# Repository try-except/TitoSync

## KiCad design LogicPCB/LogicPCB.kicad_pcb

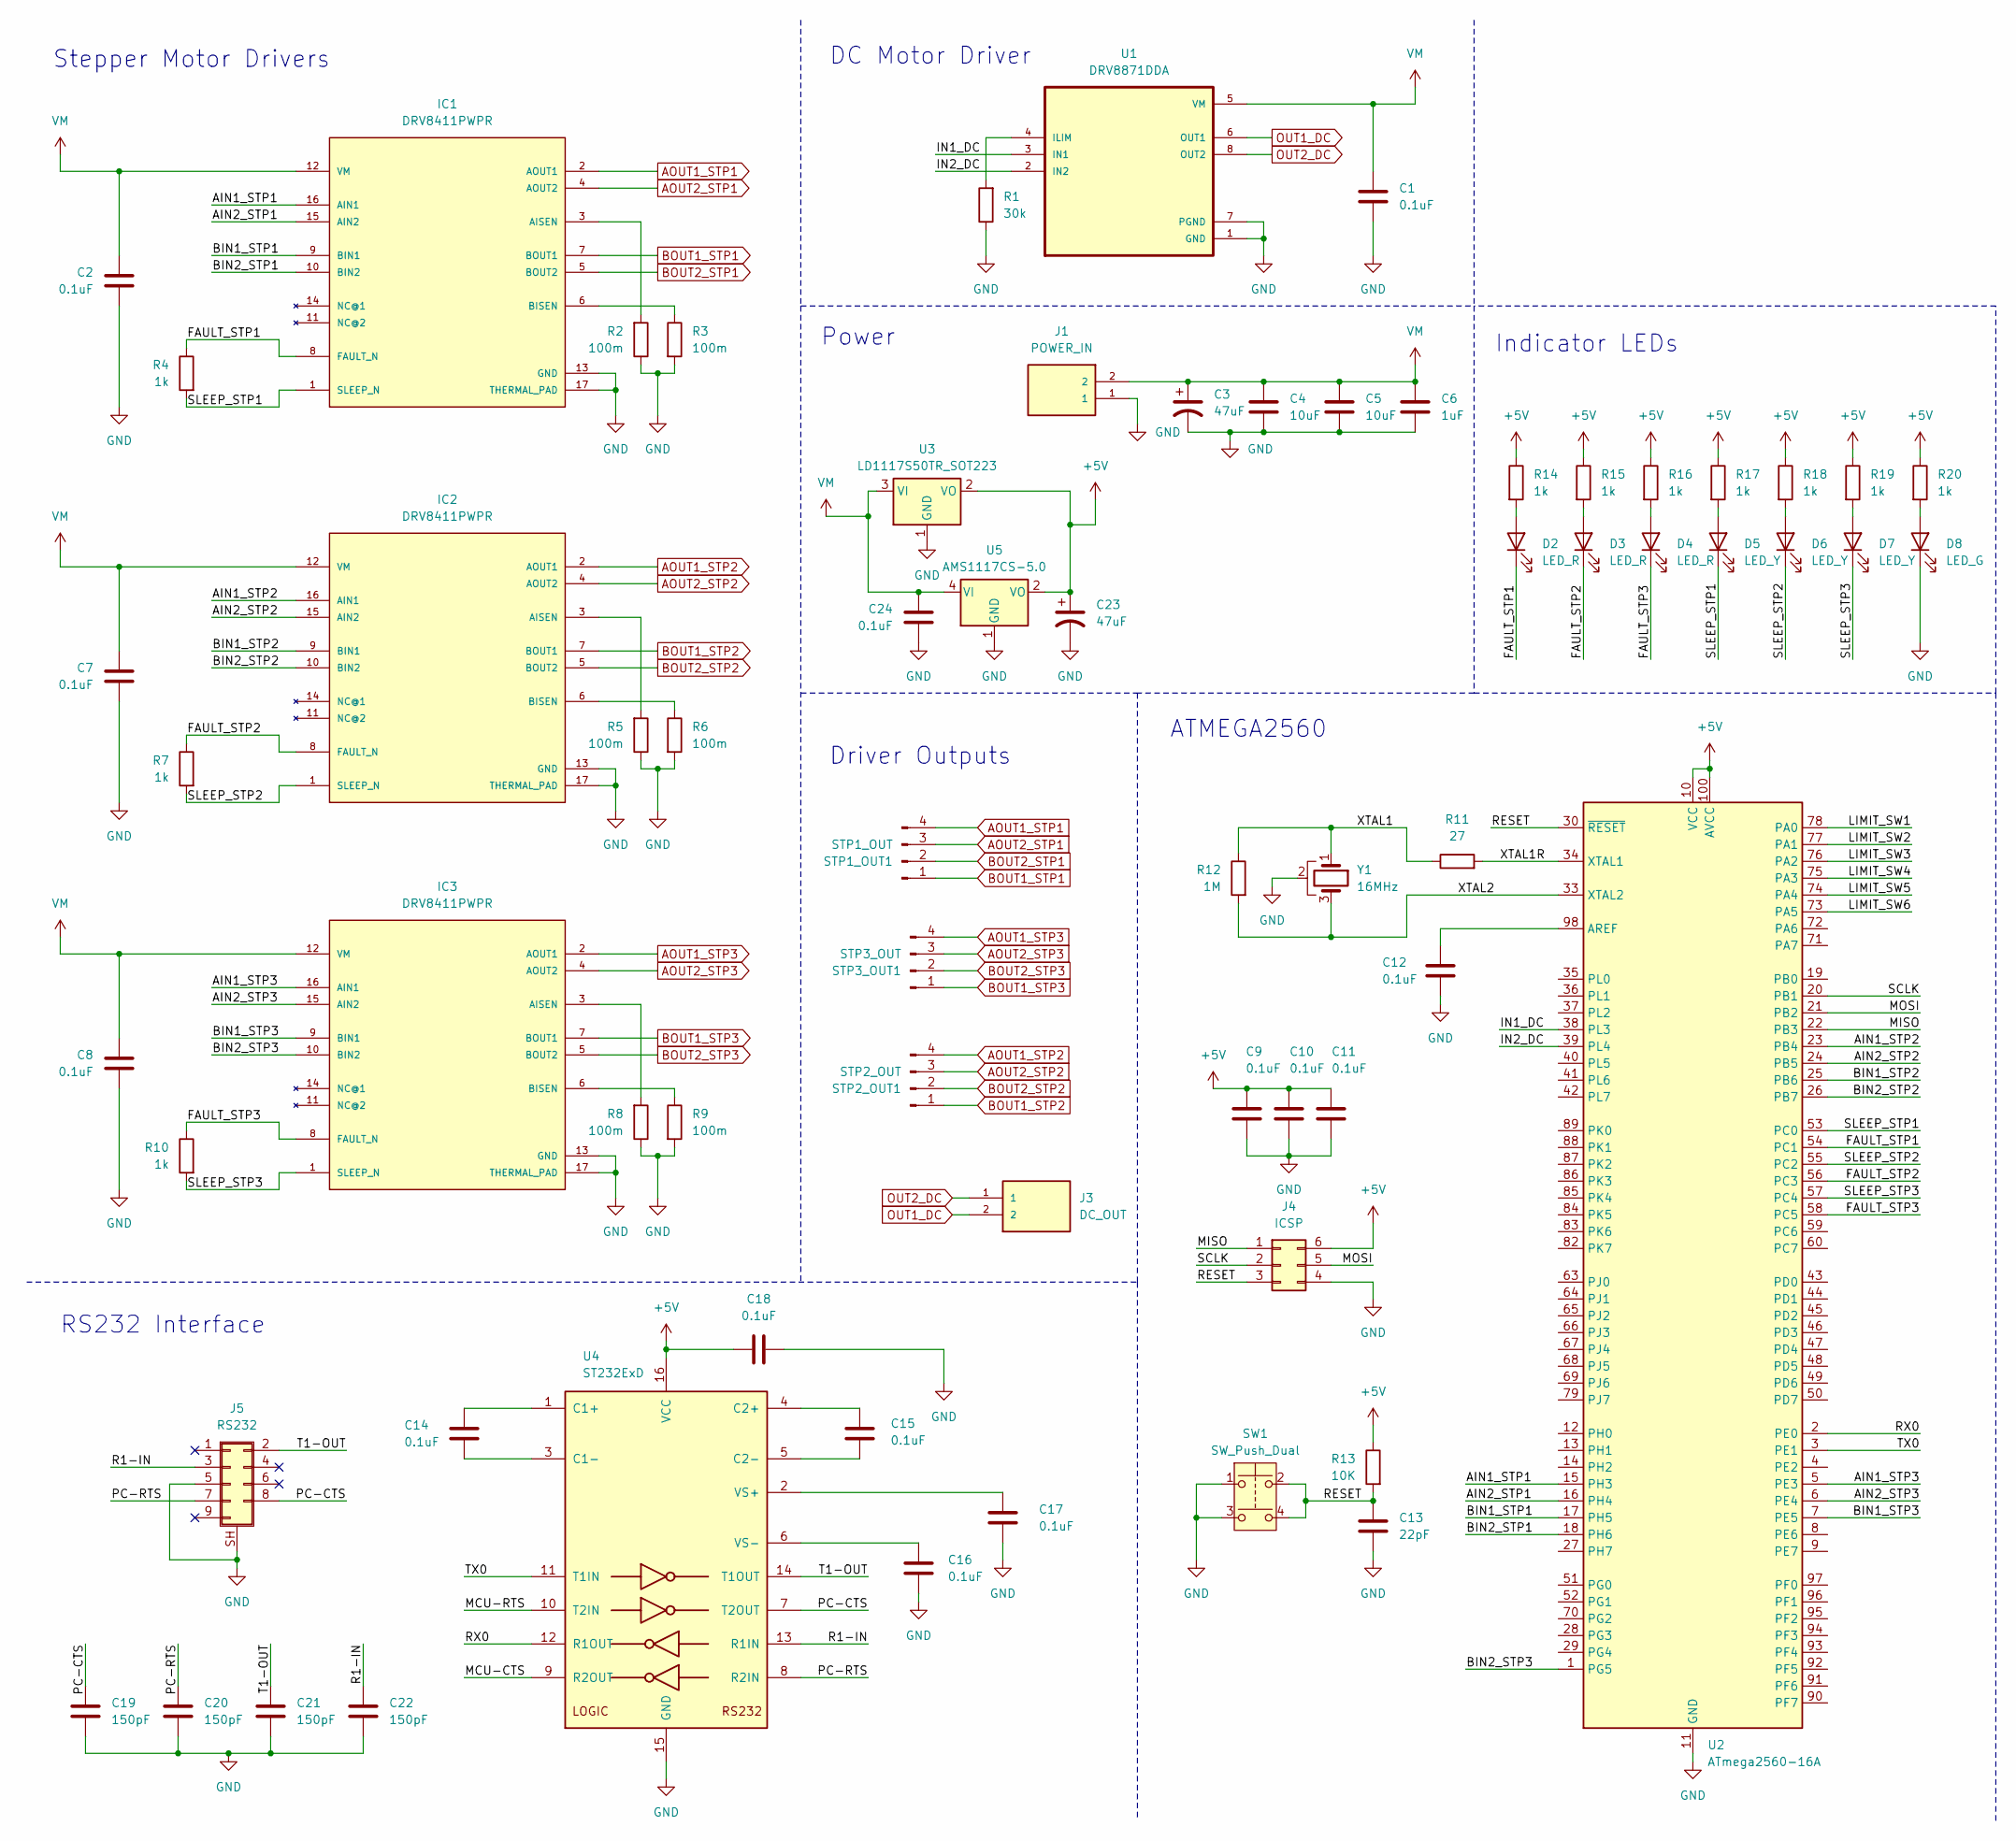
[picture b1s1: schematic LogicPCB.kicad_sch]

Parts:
C1, C2, C7, C8, C9, C10, C11, C12, C14, C15, C16, C17, C18, C24: 0.1uF; C_0402_1005Metric; PartNumber GRM155R71H104KE14D
C3, C23: 47uF; CP_Elec_6.3x5.4; PartNumber FVH035ADA470M0654
C4, C5: 10uF; C_1206_3216Metric; PartNumber C3216X7R1C106KT000N
C6: 1uF; C_0603_1608Metric; PartNumber GRT188R61H105ME13D
C13: 22pF; C_0402_1005Metric; PartNumber GRM155R71H104KE14D
C19, C20, C21, C22: 150pF; C_0402_1005Metric; PartNumber GRM1555C1H151JA01D
D2, D3, D4: LED_R; LED_0603_1608Metric
D5, D6, D7: LED_Y; LED_0603_1608Metric
D8: LED_G; LED_0603_1608Metric
IC1, IC2, IC3: DRV8411PWPR; HTSSOP-16-1EP_4.4x5mm_P0.65mm_EP3.4x5mm_Mask2.66x2.46mm; PartNumber DRV8411PWPR
J1: POWER_IN; TerminalBlock_MetzConnect_Type094_RT03502HBLU_1x02_P5.00mm_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; PARTREV 1.0
J3: DC_OUT; TerminalBlock_MetzConnect_Type094_RT03502HBLU_1x02_P5.00mm_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; PARTREV 1.0
J4: ICSP; PinHeader_2x03_P2.54mm_Vertical
J5: RS232; DSUB-9_Pins_Horizontal_P2.77x2.84mm_EdgePinOffset4.94mm_Hou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
R1: 30k; R_0805_2012Metric_Pad1.20x1.40mm_HandSolder; PartNumber 0805W8F3002T5E
R2, R3, R5, R6, R8, R9: 100m; R_1206_3216Metric; PartNumber 1206W4F100LT5E
R4, R7, R10, R14, R15, R16, R17, R18, R19, R20: 1k; R_0805_2012Metric; PartNumber 0805W8F1001T5E
R11: 27; R_0805_2012Metric
R12: 1M; R_0805_2012Metric
R13: 10K; R_0805_2012Metric
STP1_OUT1: STP1_OUT; JST_XH_B4B-XH-A_1x04_P2.50mm_Vertical
STP2_OUT1: STP2_OUT; JST_XH_B4B-XH-A_1x04_P2.50mm_Vertical
STP3_OUT1: STP3_OUT; JST_XH_B4B-XH-A_1x04_P2.50mm_Vertical
SW1: SW_Push_Dual; SW_Push_1P1T_NO_E-Switch_TL3301NxxxxxG
U1: DRV8871DDA; VREG_LM5017MR_NOPB; PartNumber DRV8871DDA
U2: ATmega2560-16A; TQFP-100_14x14mm_P0.5mm
U3: LD1117S50TR_SOT223; SOT-223-3_TabPin2
U4: ST232ExD; SOIC-16_3.9x9.9mm_P1.27mm
U5: AMS1117CS-5.0; SOIC-8_3.9x4.9mm_P1.27mm
Y1: 16MHz; Resonator_SMD_Murata_CSTxExxV-3Pin_3.0x1.1mm; PartNumber CSTNE16M0V530000R0

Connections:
+5V: C9.2, C10.2, C11.2, C18.1, C23.1, J4.6, R13.1, R14.1, R15.1, R16.1, R17.1, R18.1, R19.1, R20.1, U2.10 (VCC), U2.31 (VCC), U2.61 (VCC), U2.80 (VCC), U2.100 (AVCC), U3.2 (VO), U4.16 (VCC), U5.2 (VO), U5.3 (VO), U5.6 (VO), U5.7 (VO)
/AIN1_STP1: IC1.16 (AIN1), U2.15 (PH3)
/AIN1_STP2: IC2.16 (AIN1), U2.23 (PB4)
/AIN1_STP3: IC3.16 (AIN1), U2.5 (PE3)
/AIN2_STP1: IC1.15 (AIN2), U2.16 (PH4)
/AIN2_STP2: IC2.15 (AIN2), U2.24 (PB5)
/AIN2_STP3: IC3.15 (AIN2), U2.6 (PE4)
/BIN1_STP1: IC1.9 (BIN1), U2.17 (PH5)
/BIN1_STP2: IC2.9 (BIN1), U2.25 (PB6)
/BIN1_STP3: IC3.9 (BIN1), U2.7 (PE5)
/BIN2_STP1: IC1.10 (BIN2), U2.18 (PH6)
/BIN2_STP2: IC2.10 (BIN2), U2.26 (PB7)
/BIN2_STP3: IC3.10 (BIN2), U2.1 (PG5)
/FAULT_STP1: D2.1 (K), IC1.8 (FAULT_N), R4.1, U2.54 (PC1)
/FAULT_STP2: D3.1 (K), IC2.8 (FAULT_N), R7.1, U2.56 (PC3)
/FAULT_STP3: D4.1 (K), IC3.8 (FAULT_N), R10.1, U2.58 (PC5)
/IN1_DC: U1.3 (IN1), U2.38 (PL3)
/IN2_DC: U1.2 (IN2), U2.39 (PL4)
/LIMIT_SW1: U2.78 (PA0)
/LIMIT_SW2: U2.77 (PA1)
/LIMIT_SW3: U2.76 (PA2)
/LIMIT_SW4: U2.75 (PA3)
/LIMIT_SW5: U2.74 (PA4)
/LIMIT_SW6: U2.73 (PA5)
/MCU-CTS: U4.9 (R2OUT)
/MCU-RTS: U4.10 (T2IN)
/MISO: J4.1, U2.22 (PB3)
/MOSI: J4.5, U2.21 (PB2)
/PC-CTS: C19.1, J5.8, U4.7 (T2OUT)
/PC-RTS: C20.1, J5.7, U4.8 (R2IN)
/R1-IN: C22.1, J5.3, U4.13 (R1IN)
/RESET: C13.2, J4.3, R13.2, SW1.2, SW1.4, U2.30 (~RESET); also elsewhere on the board
/RX0: U2.2 (PE0), U4.12 (R1OUT)
/SCLK: J4.2, U2.20 (PB1)
/SLEEP_STP1: D5.1 (K), IC1.1 (SLEEP_N), R4.2, U2.53 (PC0)
/SLEEP_STP2: D6.1 (K), IC2.1 (SLEEP_N), R7.2, U2.55 (PC2)
/SLEEP_STP3: D7.1 (K), IC3.1 (SLEEP_N), R10.2, U2.57 (PC4)
/T1-OUT: C21.1, J5.2, U4.14 (T1OUT)
/TX0: U2.3 (PE1), U4.11 (T1IN)
/XTAL1: R11.1, R12.1, Y1.1
/XTAL1R: R11.2, U2.34 (XTAL1)
/XTAL2: R12.2, U2.33 (XTAL2), Y1.3
AOUT1_STP1: IC1.2 (AOUT1), STP1_OUT1.4; also elsewhere on the board
AOUT1_STP2: IC2.2 (AOUT1), STP2_OUT1.4; also elsewhere on the board
AOUT1_STP3: IC3.2 (AOUT1), STP3_OUT1.4; also elsewhere on the board
AOUT2_STP1: IC1.4 (AOUT2), STP1_OUT1.3; also elsewhere on the board
AOUT2_STP2: IC2.4 (AOUT2), STP2_OUT1.3; also elsewhere on the board
AOUT2_STP3: IC3.4 (AOUT2), STP3_OUT1.3; also elsewhere on the board
BOUT1_STP1: IC1.7 (BOUT1), STP1_OUT1.1; also elsewhere on the board
BOUT1_STP2: IC2.7 (BOUT1), STP2_OUT1.1; also elsewhere on the board
BOUT1_STP3: IC3.7 (BOUT1), STP3_OUT1.1; also elsewhere on the board
BOUT2_STP1: IC1.5 (BOUT2), STP1_OUT1.2; also elsewhere on the board
BOUT2_STP2: IC2.5 (BOUT2), STP2_OUT1.2; also elsewhere on the board
BOUT2_STP3: IC3.5 (BOUT2), STP3_OUT1.2; also elsewhere on the board
GND: C1.1, C2.1, C3.2, C4.1, C5.1, C6.2, C7.1, C8.1, C9.1, C10.1, C11.1, C12.1, C13.1, C16.1, C17.1, C18.2, C19.2, C20.2, C21.2, C22.2, C23.2, C24.1, D8.1 (K), IC1.13 (GND), IC1.17 (THERMAL_PAD), IC2.13 (GND), IC2.17 (THERMAL_PAD), IC3.13 (GND), IC3.17 (THERMAL_PAD), J1.1, J4.4, J5.5, J5.SH (Shield), R1.1, R2.1, R3.2, R5.1, R6.2, R8.1, R9.2, SW1.1, SW1.3, U1.1 (GND), U1.7 (PGND), U2.11 (GND), U2.32 (GND), U2.62 (GND), U2.81 (GND), U2.99 (GND), U3.1 (GND), U4.15 (GND), U5.1 (GND), Y1.2; also elsewhere on the board
unnamed: D2.2 (A), R14.2
unnamed: D3.2 (A), R15.2
unnamed: D4.2 (A), R16.2
unnamed: D5.2 (A), R17.2
unnamed: D6.2 (A), R18.2
unnamed: D7.2 (A), R19.2
unnamed: D8.2 (A), R20.2
unnamed: IC1.3 (AISEN), R2.2
unnamed: IC1.6 (BISEN), R3.1
unnamed: IC2.3 (AISEN), R5.2
unnamed: IC2.6 (BISEN), R6.1
unnamed: IC3.3 (AISEN), R8.2
unnamed: IC3.6 (BISEN), R9.1
unnamed: R1.2, U1.4 (ILIM)
unnamed: C12.2, U2.98 (AREF)
unnamed: C14.2, U4.1 (C1+)
unnamed: C14.1, U4.3 (C1-)
unnamed: C15.2, U4.4 (C2+)
unnamed: C15.1, U4.5 (C2-)
unnamed: C17.2, U4.2 (VS+)
unnamed: C16.2, U4.6 (VS-)
OUT1_DC: J3.2, U1.6 (OUT1)
OUT2_DC: J3.1, U1.8 (OUT2)
VM: C1.2, C2.2, C3.1, C4.2, C5.2, C6.1, C7.2, C8.2, C24.2, IC1.12 (VM), IC2.12 (VM), IC3.12 (VM), J1.2, U1.5 (VM), U3.3 (VI), U5.4 (VI)

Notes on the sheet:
DC Motor Driver
Stepper Motor Drivers
Indicator LEDs
ATMEGA2560
RS232 Interface
Driver Outputs
Power

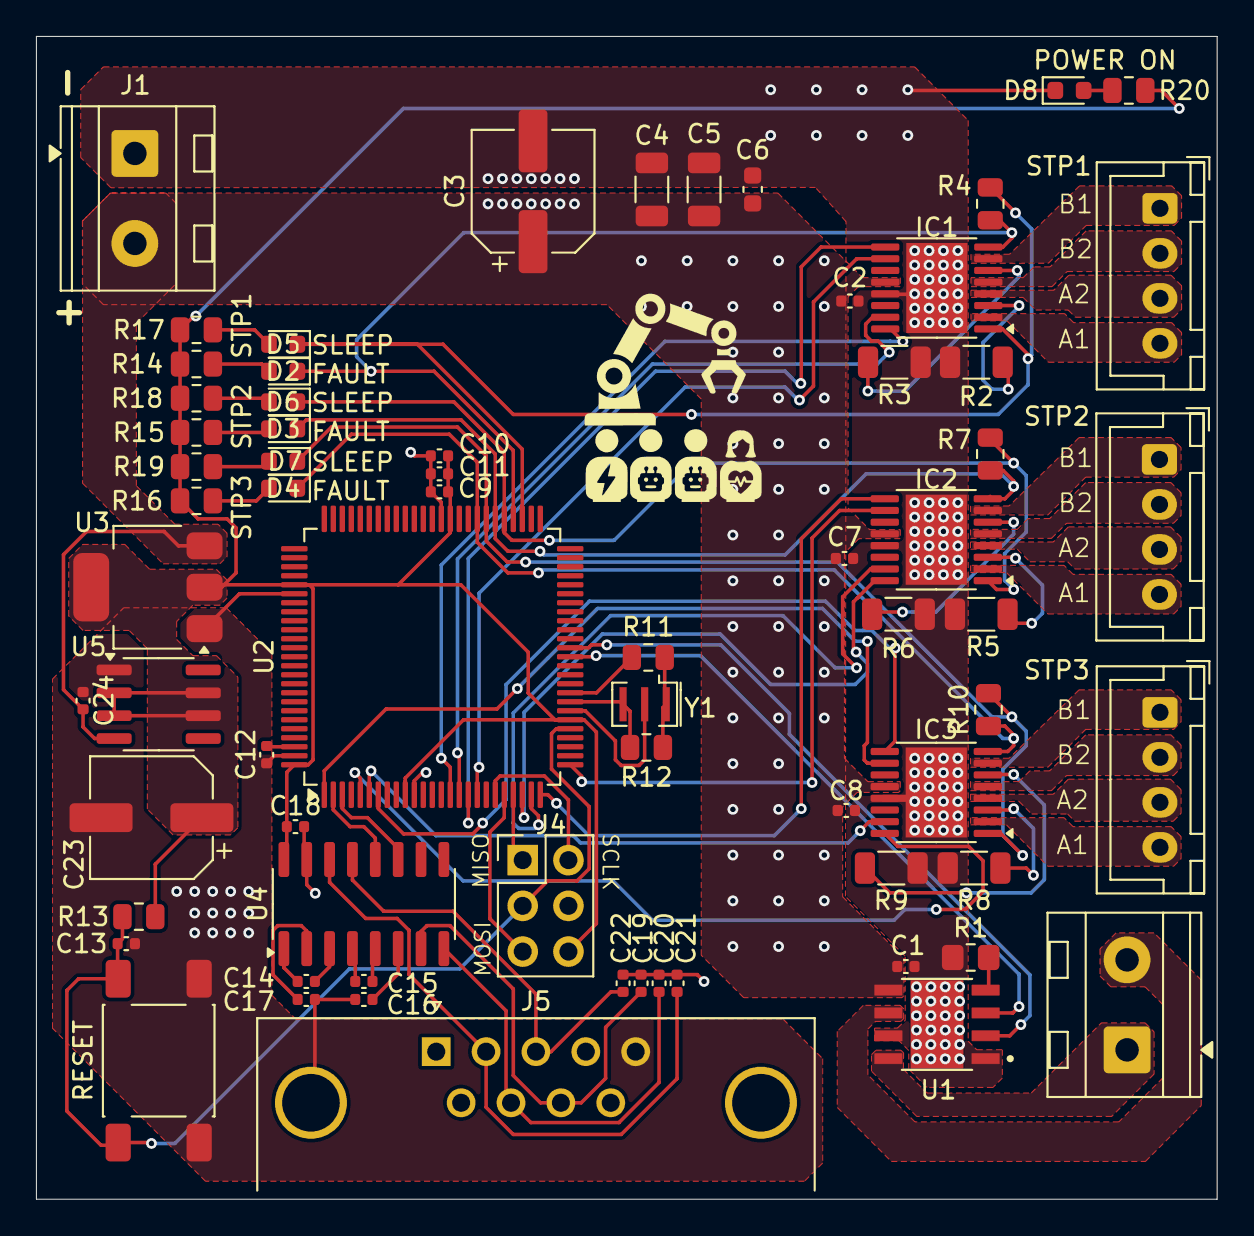
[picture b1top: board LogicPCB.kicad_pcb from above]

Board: 2 copper layers, 65.6 x 64.6 mm, 68 parts (0 on the bottom side), 71 nets.

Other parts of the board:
RESET: SW_Push_Dual; SW_Push_1P1T_NO_E-Switch_TL3301NxxxxxG
STP1: STP1_OUT; JST_XH_B4B-XH-A_1x04_P2.50mm_Vertical
STP2: STP2_OUT; JST_XH_B4B-XH-A_1x04_P2.50mm_Vertical
STP3: STP3_OUT; JST_XH_B4B-XH-A_1x04_P2.50mm_Vertical

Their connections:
/RESET: RESET.2; also elsewhere on the board
AOUT1_STP1: STP1.4; also elsewhere on the board
AOUT1_STP2: STP2.4; also elsewhere on the board
AOUT1_STP3: STP3.4; also elsewhere on the board
AOUT2_STP1: STP1.3; also elsewhere on the board
AOUT2_STP2: STP2.3; also elsewhere on the board
AOUT2_STP3: STP3.3; also elsewhere on the board
BOUT1_STP1: STP1.1; also elsewhere on the board
BOUT1_STP2: STP2.1; also elsewhere on the board
BOUT1_STP3: STP3.1; also elsewhere on the board
BOUT2_STP1: STP1.2; also elsewhere on the board
BOUT2_STP2: STP2.2; also elsewhere on the board
BOUT2_STP3: STP3.2; also elsewhere on the board
GND: RESET.1; also elsewhere on the board

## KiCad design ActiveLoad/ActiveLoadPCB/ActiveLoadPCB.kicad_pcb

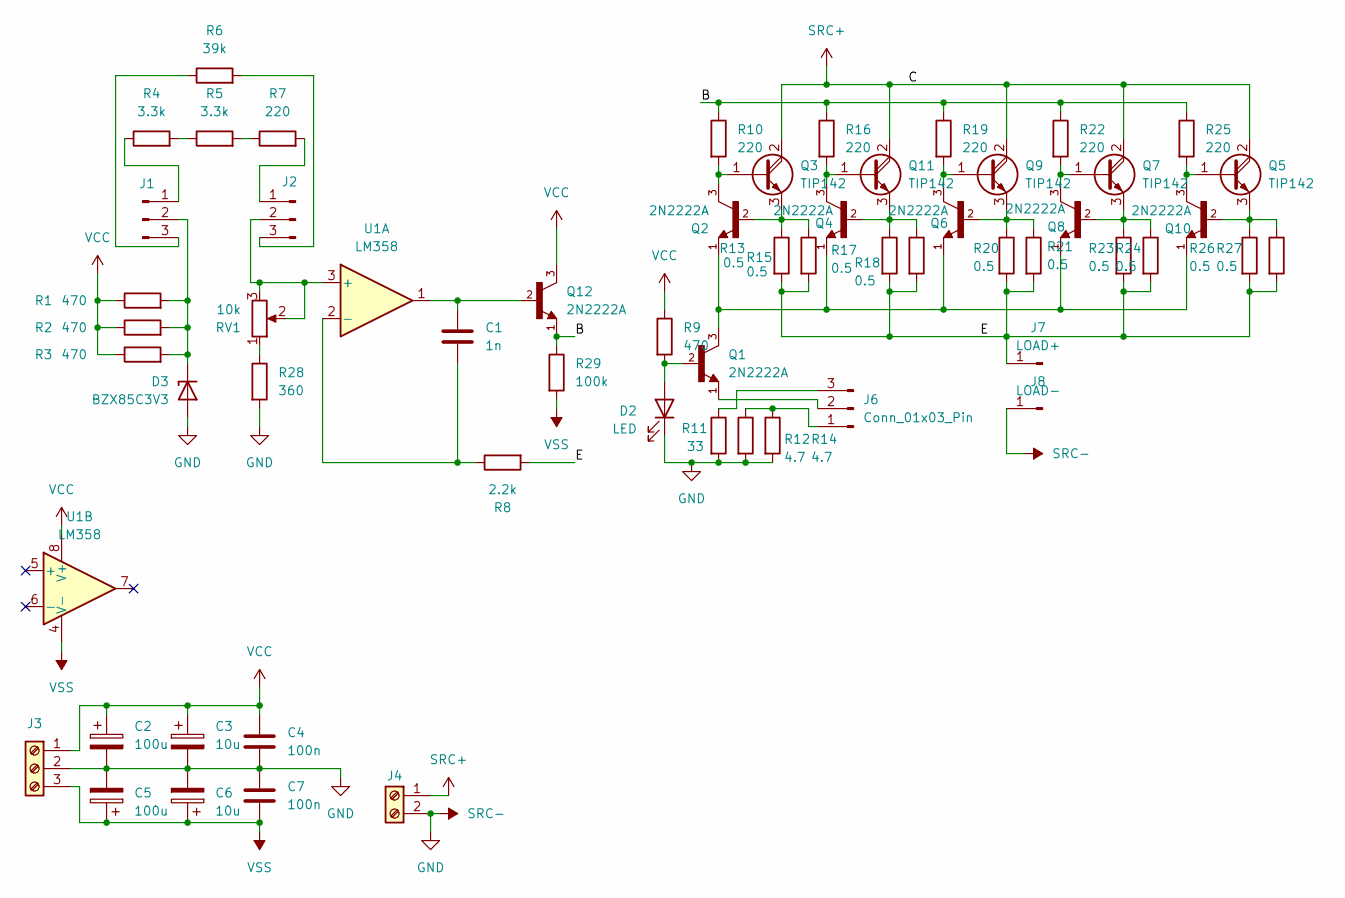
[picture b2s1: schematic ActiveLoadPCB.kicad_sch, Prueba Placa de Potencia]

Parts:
C1: 1n; C_Disc_D5.0mm_W2.5mm_P2.50mm
C2, C5: 100u; CP_Radial_D5.0mm_P2.50mm
C3, C6: 10u; CP_Radial_D5.0mm_P2.50mm
C4, C7: 100n; C_Disc_D5.0mm_W2.5mm_P2.50mm
D2: LED; LED_D3.0mm
D3: BZX85C3V3; D_T-1_P5.08mm_Horizontal
J1, J2, J6: Conn_01x03_Pin; PinHeader_1x03_P2.54mm_Vertical
J3: Screw_Terminal_01x03; TerminalBlock_MetzConnect_Type055_RT01503HDWU_1x03_P5.00mm_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
J4: Screw_Terminal_01x02; TerminalBlock_MetzConnect_Type055_RT01502HDWU_1x02_P5.00mm_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
J7: LOAD+; MountingHole_4.3mm_M4_DIN965_Pad
J8: LOAD-; MountingHole_4.3mm_M4_DIN965_Pad
Q1, Q2, Q4, Q6, Q8, Q10, Q12: 2N2222A; TO-92L_Inline_Wide; PARTREV N/A
Q3, Q5, Q7, Q9, Q11: TIP142; TO-247-3_Vertical
R1, R2, R3, R9: 470; R_Axial_DIN0207_L6.3mm_D2.5mm_P7.62mm_Horizontal
R4, R5: 3.3k; R_Axial_DIN0207_L6.3mm_D2.5mm_P7.62mm_Horizontal
R6: 39k; R_Axial_DIN0207_L6.3mm_D2.5mm_P7.62mm_Horizontal
R7, R10, R16, R19, R22, R25: 220; R_Axial_DIN0207_L6.3mm_D2.5mm_P7.62mm_Horizontal
R8: 2.2k; R_Axial_DIN0207_L6.3mm_D2.5mm_P7.62mm_Horizontal
R11: 33; R_Axial_DIN0207_L6.3mm_D2.5mm_P7.62mm_Horizontal
R12, R14: 4.7; R_Axial_DIN0207_L6.3mm_D2.5mm_P7.62mm_Horizontal
R13, R15, R17, R18, R20, R21, R23, R24, R26, R27: 0.5; R_Axial_DIN0309_L9.0mm_D3.2mm_P12.70mm_Horizontal
R28: 360; R_Axial_DIN0207_L6.3mm_D2.5mm_P7.62mm_Horizontal
R29: 100k; R_Axial_DIN0207_L6.3mm_D2.5mm_P7.62mm_Horizontal
RV1: 10k; Potentiometer
U1: LM358; DIP-8_W7.62mm_Socket

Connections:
/B: Q12.1, R10.1, R16.1, R19.1, R22.1, R25.1, R29.1
/E: J7.1, R8.2, R13.2, R15.2, R17.2, R18.2, R20.2, R21.2, R23.2, R24.2, R26.2, R27.2
GND: C2.2, C3.2, C4.2, C5.2, C6.2, C7.1, D2.1 (K), D3.2 (A), J3.2, J4.2, J8.1, R11.2, R12.2, R14.2, R28.2
unnamed: C1.1, Q12.2, U1.1
unnamed: D2.2 (A), Q1.2, R9.2
unnamed: D3.1 (K), J1.2, R1.2, R2.2, R3.2
unnamed: J1.1, R4.1
unnamed: J1.3, R6.1
unnamed: J2.1, R7.2
unnamed: J2.2, RV1.2, RV1.3, U1.3 (+)
unnamed: J2.3, R6.2
unnamed: J6.1, R12.1, R14.1
unnamed: J6.2, Q1.1
unnamed: J6.3, R11.1
unnamed: Q1.3, Q2.1, Q4.1, Q6.1, Q8.1, Q10.1
unnamed: Q2.3, Q3.1 (B), R10.2
unnamed: Q2.2, Q3.3 (E), R13.1, R15.1
unnamed: Q5.1 (B), Q10.3, R25.2
unnamed: Q5.3 (E), Q10.2, R26.1, R27.1
unnamed: Q7.1 (B), Q8.3, R22.2
unnamed: Q7.3 (E), Q8.2, R23.1, R24.1
unnamed: Q6.3, Q9.1 (B), R19.2
unnamed: Q6.2, Q9.3 (E), R20.1, R21.1
unnamed: Q4.3, Q11.1 (B), R16.2
unnamed: Q4.2, Q11.3 (E), R17.1, R18.1
unnamed: R4.2, R5.1
unnamed: R5.2, R7.1
unnamed: R28.1, RV1.1
unnamed: C1.2, R8.1, U1.2 (-)
SRC+: J4.1, Q3.2 (C), Q5.2 (C), Q7.2 (C), Q9.2 (C), Q11.2 (C)
VCC: C2.1, C3.1, C4.1, J3.1, Q12.3, R1.1, R2.1, R3.1, R9.1, U1.8 (V+)
VSS: C5.1, C6.1, C7.2, J3.3, R29.2, U1.4 (V-), U1.6 (-)

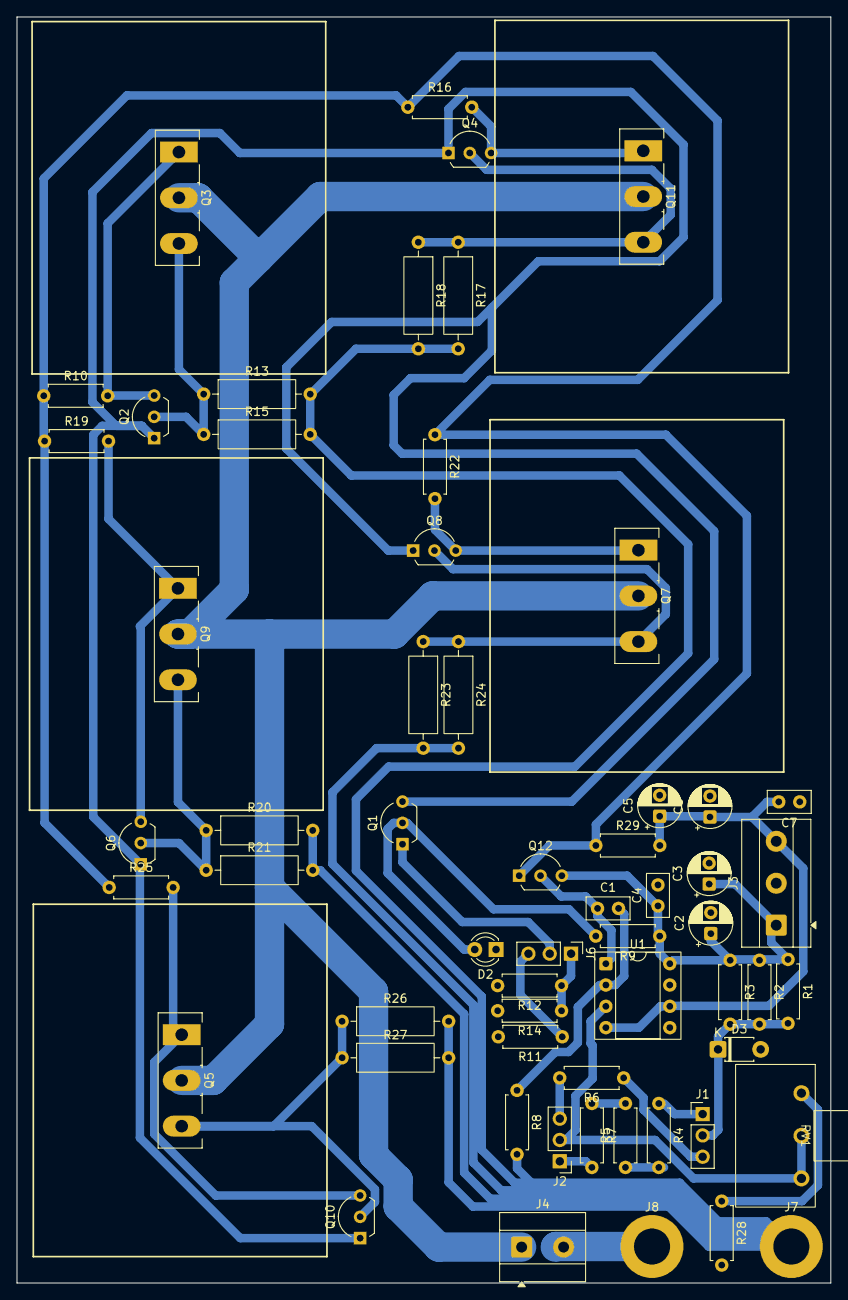
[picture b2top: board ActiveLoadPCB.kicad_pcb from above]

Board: 2 copper layers, 97.0 x 150.9 mm, 59 parts (0 on the bottom side), 32 nets.

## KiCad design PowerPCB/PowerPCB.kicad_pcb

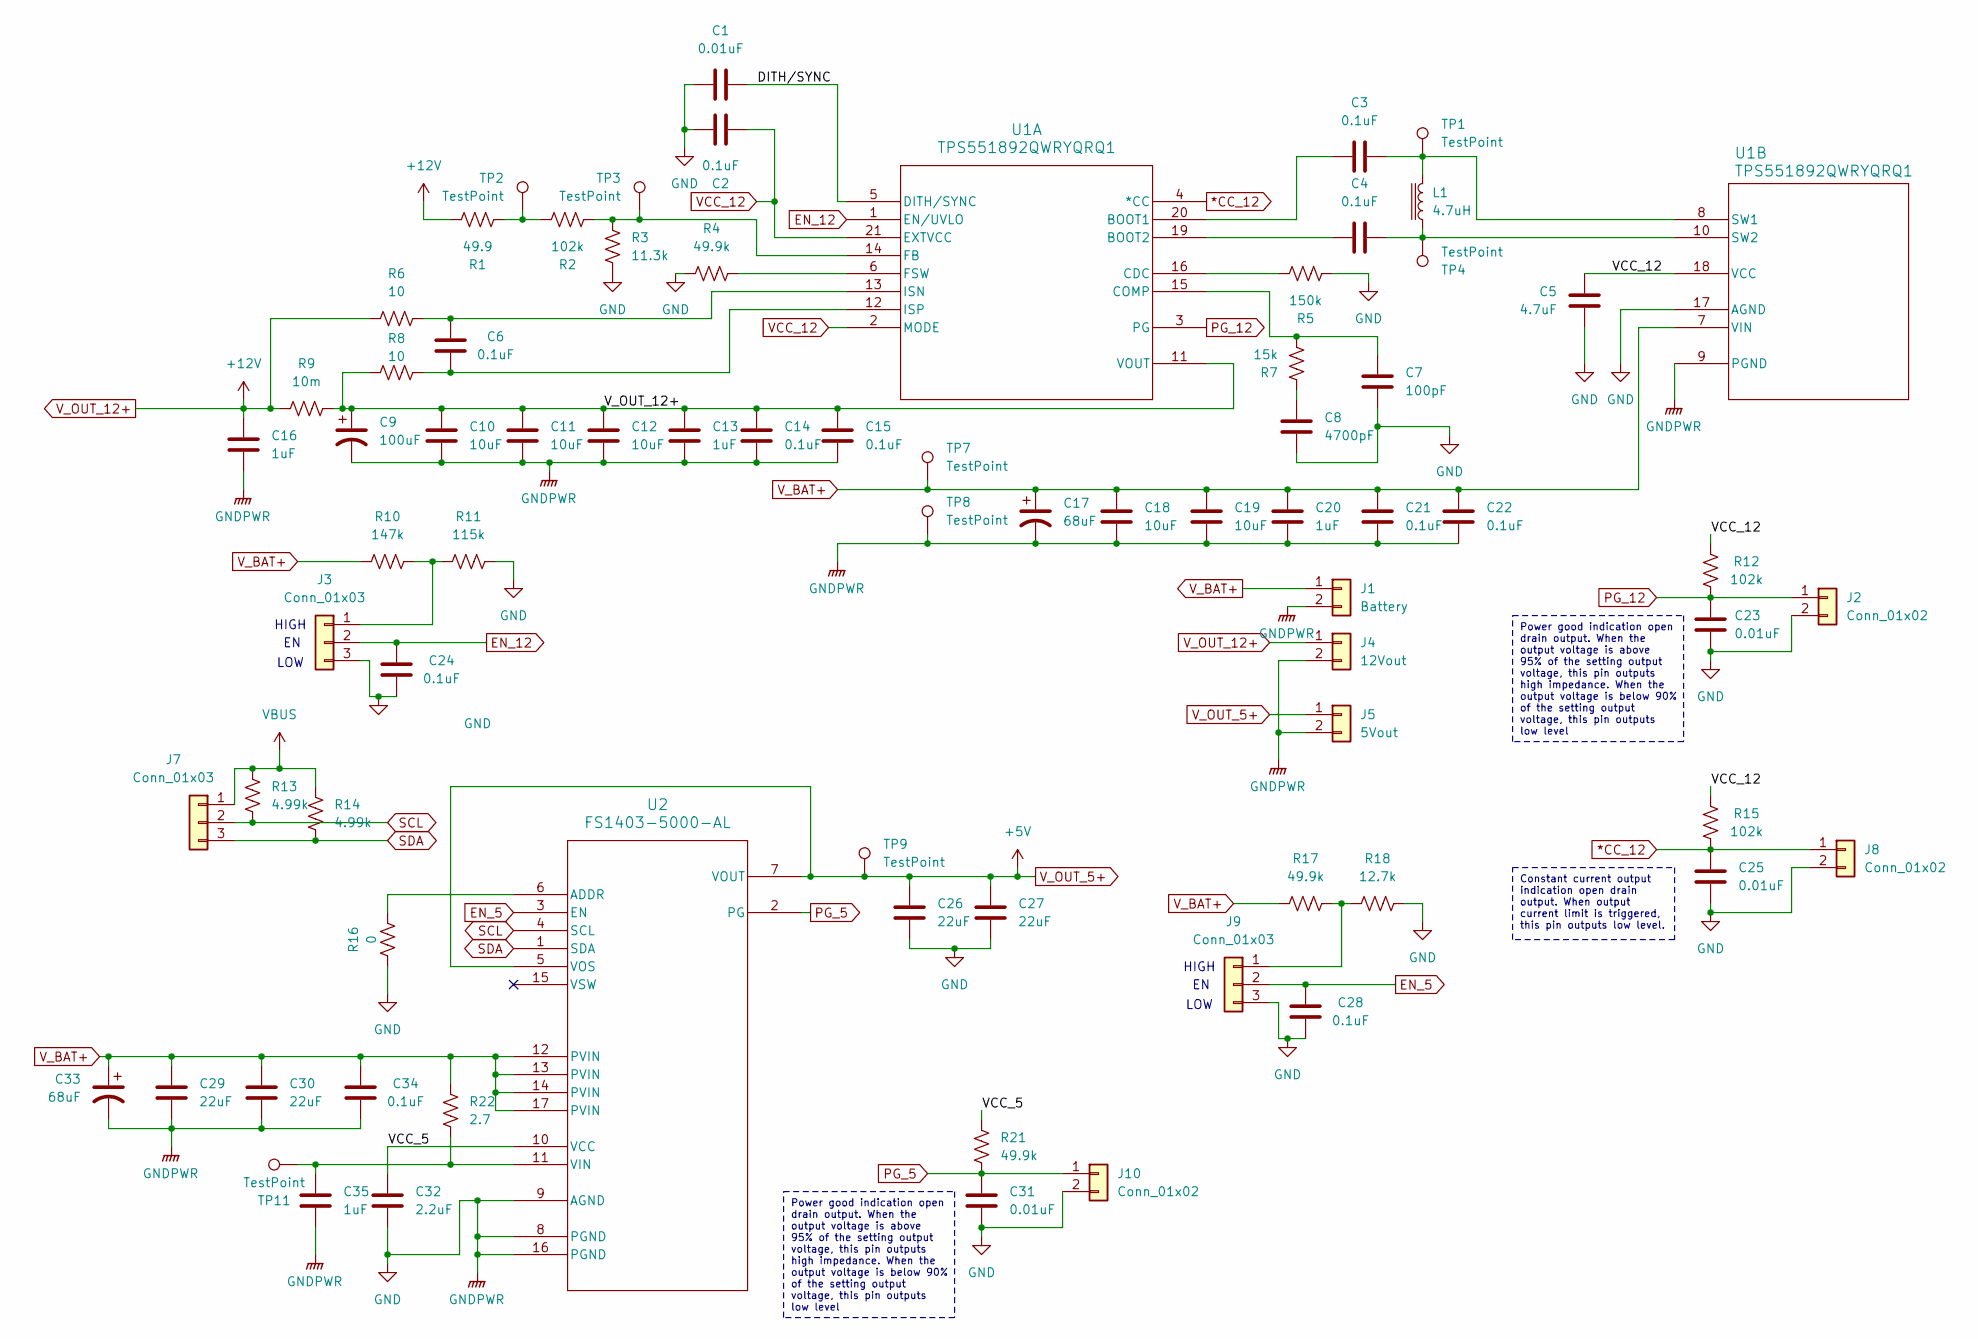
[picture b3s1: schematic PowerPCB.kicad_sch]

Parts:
C1, C23, C25, C31: 0.01uF; C_0402_1005Metric; PartNumber CGA2B3X7R1H103K050BB; LCSC C248318
C2, C6, C24, C28, C34: 0.1uF; C_0402_1005Metric; PartNumber C1005X7R1H104KT000F; LCSC C361198
C3, C4: 0.1uF; C_0603_1608Metric; PartNumber GCM188L81H104KA57D; LCSC C161181
C5: 4.7uF; C_0603_1608Metric; PartNumber GRT188R61C475KE13D; LCSC C437574
C7: 100pF; C_0402_1005Metric; PartNumber CGA2B2C0G1H101J050BA; LCSC C2162824
C8: 4700pF; C_0402_1005Metric; PartNumber C1005X7R1H472KT000F; LCSC C694277
C9: 100uF; CP_Elec_6.3x5.8; PartNumber EEHZK1V101XP; LCSC C454360
C10, C11, C12, C18, C19: 10uF; C_1206_3216Metric; PartNumber CGA5L1X7R1H106K160AC; LCSC C342827
C13, C16, C20, C35: 1uF; C_0603_1608Metric; PartNumber GRT188R61H105ME13D; LCSC C3011671
C14, C15, C21, C22: 0.1uF; C_0402_1005Metric; PartNumber GRM155R71H104KE14D; LCSC C77020
C17, C33: 68uF; CP_Elec_8x10; PartNumber EEHZA1H680P; LCSC C542443
C26, C27, C29, C30: 22uF; C_1206_3216Metric; PartNumber CGA5L1X7S1A226M160AC; LCSC C2182087
C32: 2.2uF; C_1206_3216Metric; PartNumber TCC1206X7R225M250HT; LCSC C5449010
J1: Battery; TerminalBlock_MetzConnect_Type094_RT03502HBLU_1x02_P5.00mm_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; PartNumber DB102-5.0-2P-BU-S; LCSC C7498454
J2, J8, J10: Conn_01x02; PinHeader_1x02_P2.54mm_Vertical; PartNumber HX PH254-01-02-Z-L11.5 male header conn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; LCSC C52016390
J3, J7, J9: Conn_01x03; PinHeader_1x03_P2.54mm_Vertical; PartNumber HX PH254-01-03-Z-L11.5 pcb pin header; LCSC C52016391
J4: 12Vout; TerminalBlock_MetzConnect_Type094_RT03502HBLU_1x02_P5.00mm_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; PartNumber DB102-5.0-2P-BU-S; LCSC C7498454
J5: 5Vout; TerminalBlock_MetzConnect_Type094_RT03502HBLU_1x02_P5.00mm_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; PartNumber DB102-5.0-2P-BU-S; LCSC C7498454
L1: 4.7uH; L_Coilcraft_XAL7070-XXX; PartNumber XAL7070-472MEB; LCSC C3911513
R1: 49.9; R_0402_1005Metric; PartNumber CRCW040249R9FKED; LCSC C482189
R2, R12, R15: 102k; R_0402_1005Metric; PartNumber CRCW0402102KFKED; LCSC C481920
R3: 11.3k; R_0402_1005Metric; PartNumber CRCW040211K3FKED; LCSC C481933
R4, R17, R21: 49.9k; R_0402_1005Metric; PartNumber CRCW040249K9FKED; LCSC C350874
R5: 150k; R_0402_1005Metric; PartNumber AECR0402F150KK9; LCSC C328301
R6, R8: 10; R_0402_1005Metric; PartNumber CRCW040210R0FKED; LCSC C481926
R7: 15k; R_0402_1005Metric; PartNumber CRCW040215K0FKED; LCSC C191587
R9: 10m; R_1206_3216Metric; PartNumber CRF1206-FZ-R010ELF; LCSC C5629523
R10: 147k; R_0402_1005Metric; PartNumber FRC0402F1473TS; LCSC C2933073
R11: 115k; R_0402_1005Metric; PartNumber CRCW0402115KFKED; LCSC C2076632
R13, R14: 4.99k; R_0402_1005Metric; PartNumber CRCW04024K99FKED; LCSC C482195
R16: 0; R_0402_1005Metric; PartNumber CRCW04020000Z0EDHP; LCSC C844711
R18: 12.7k; R_0402_1005Metric; PartNumber CRCW040212K7FKED; LCSC C481941
R22: 2.7; R_0402_1005Metric; PartNumber CRCW040227R0FKED; LCSC C482122
TP1, TP2, TP3, TP4, TP7, TP8, TP9, TP11: TestPoint; TestPoint_Keystone_5019_Miniature; PartNumber 5019; LCSC C238131
U1: TPS551892QWRYQRQ1; VQFN21_RYQ_TEX; PartNumber TPS551892QWRYQRQ1; LCSC C42116949
U2: FS1403-5000-AL; FS1403_TDK; PartNumber FS1403-5000-AL; LCSC C6253250

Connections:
*CC_12: C25.2, J8.1, R15.1, U1.4 (*CC)
/DITH/SYNC: C1.2, U1.5 (DITH/SYNC)
/VCC_5: C32.1, R21.1, U2.10 (VCC)
EN_5: C28.2, J9.2, U2.3 (EN)
EN_12: C24.2, J3.2, U1.1 (EN/UVLO)
GND: C1.1, C2.1, C5.2, C7.2, C8.2, C9.2, C10.2, C11.2, C12.2, C13.2, C14.2, C15.2, C16.2, C17.2, C18.2, C19.2, C20.2, C21.2, C22.2, C23.1, C24.1, C25.1, C26.2, C27.2, C28.1, C29.2, C30.2, C31.2, C32.2, C33.2, C34.1, C35.2, J1.2, J2.2, J3.3, J4.2, J5.2, J8.2, J9.3, J10.2, R3.1, R4.2, R5.2, R11.2, R16.1, R18.2, TP8.1, U1.9 (PGND), U1.17 (AGND), U2.8 (PGND), U2.9 (AGND), U2.16 (PGND); also elsewhere on the board
unnamed: C8.1, R7.1
unnamed: J3.1, R10.2, R11.1
unnamed: J9.1, R17.2, R18.1
unnamed 9: R1.2, R2.1, TP2.1; also elsewhere on the board
unnamed: C3.1, U1.20 (BOOT1)
unnamed: C4.1, U1.19 (BOOT2)
unnamed: R5.1, U1.16 (CDC)
unnamed: C7.1, R7.2, U1.15 (COMP)
unnamed 14: R2.2, R3.2, TP3.1, U1.14 (FB); also elsewhere on the board
unnamed: R4.1, U1.6 (FSW)
unnamed: C6.2, R6.2, U1.13 (ISN)
unnamed: C6.1, R8.2, U1.12 (ISP)
unnamed: C3.2, L1.2, TP1.1, U1.8 (SW1)
unnamed: C4.2, L1.1, TP4.1, U1.10 (SW2)
unnamed: R16.2, U2.6 (ADDR)
unnamed 21: C35.1, R22.2, TP11.1, U2.11 (VIN); also elsewhere on the board
PG_5: C31.1, J10.1, R21.2, U2.2 (PG)
PG_12: C23.2, J2.1, R12.1, U1.3 (PG)
SCL: J7.2, R13.2, U2.4 (SCL)
SDA: J7.3, R14.2, U2.1 (SDA)
VBUS: J7.1, R13.1, R14.1
VCC_12: C2.2, C5.1, R12.2, R15.2, U1.2 (MODE), U1.18 (VCC), U1.21 (EXTVCC)
V_BAT+: C17.1, C18.1, C19.1, C20.1, C21.1, C22.1, C29.1, C30.1, C33.1, C34.2, J1.1, R10.1, R17.1, R22.1, TP7.1, U1.7 (VIN), U2.12 (PVIN), U2.13 (PVIN), U2.14 (PVIN), U2.17 (PVIN); also elsewhere on the board
V_OUT_5+: C26.1, C27.1, J5.1, TP9.1, U2.5 (VOS), U2.7 (VOUT); also elsewhere on the board
V_OUT_12+: C9.1, C10.1, C11.1, C12.1, C13.1, C14.1, C15.1, C16.1, J4.1, R1.1, R6.1, R8.1, R9.1, R9.2, U1.11 (VOUT)

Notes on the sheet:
HIGH
LOW
Constant current output indication open drain output. When output current limit is triggered, this pin outputs low level.
Power good indication open drain output. When the output voltage is above 95% of the setting output voltage, this pin outputs high impedance. When the output voltage is below 90% of the setting output voltage, this pin outputs low level
